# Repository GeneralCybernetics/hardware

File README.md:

### General Cybernetics Project PCBs & CAD Models

**TODO**
- [ ] move big files to git-lfs
- [ ] move current STM32 to STM32F407VGT6

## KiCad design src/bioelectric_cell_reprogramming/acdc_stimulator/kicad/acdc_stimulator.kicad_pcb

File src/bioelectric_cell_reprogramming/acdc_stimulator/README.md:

# Ion Concentration Biomodulator
The Ion Concentration Biomodulator can precisely alter the ionic composition of extracellular fluid to modulate the $$V_{mem}$$ of cells.

### Links
- [Parts list](https://docs.google.com/spreadsheets/d/1BXY7yvE0v-gVbK3v_EXQUiAxz3EebexK3CFEh7COzpo/edit?usp=sharing) (non-PCB)

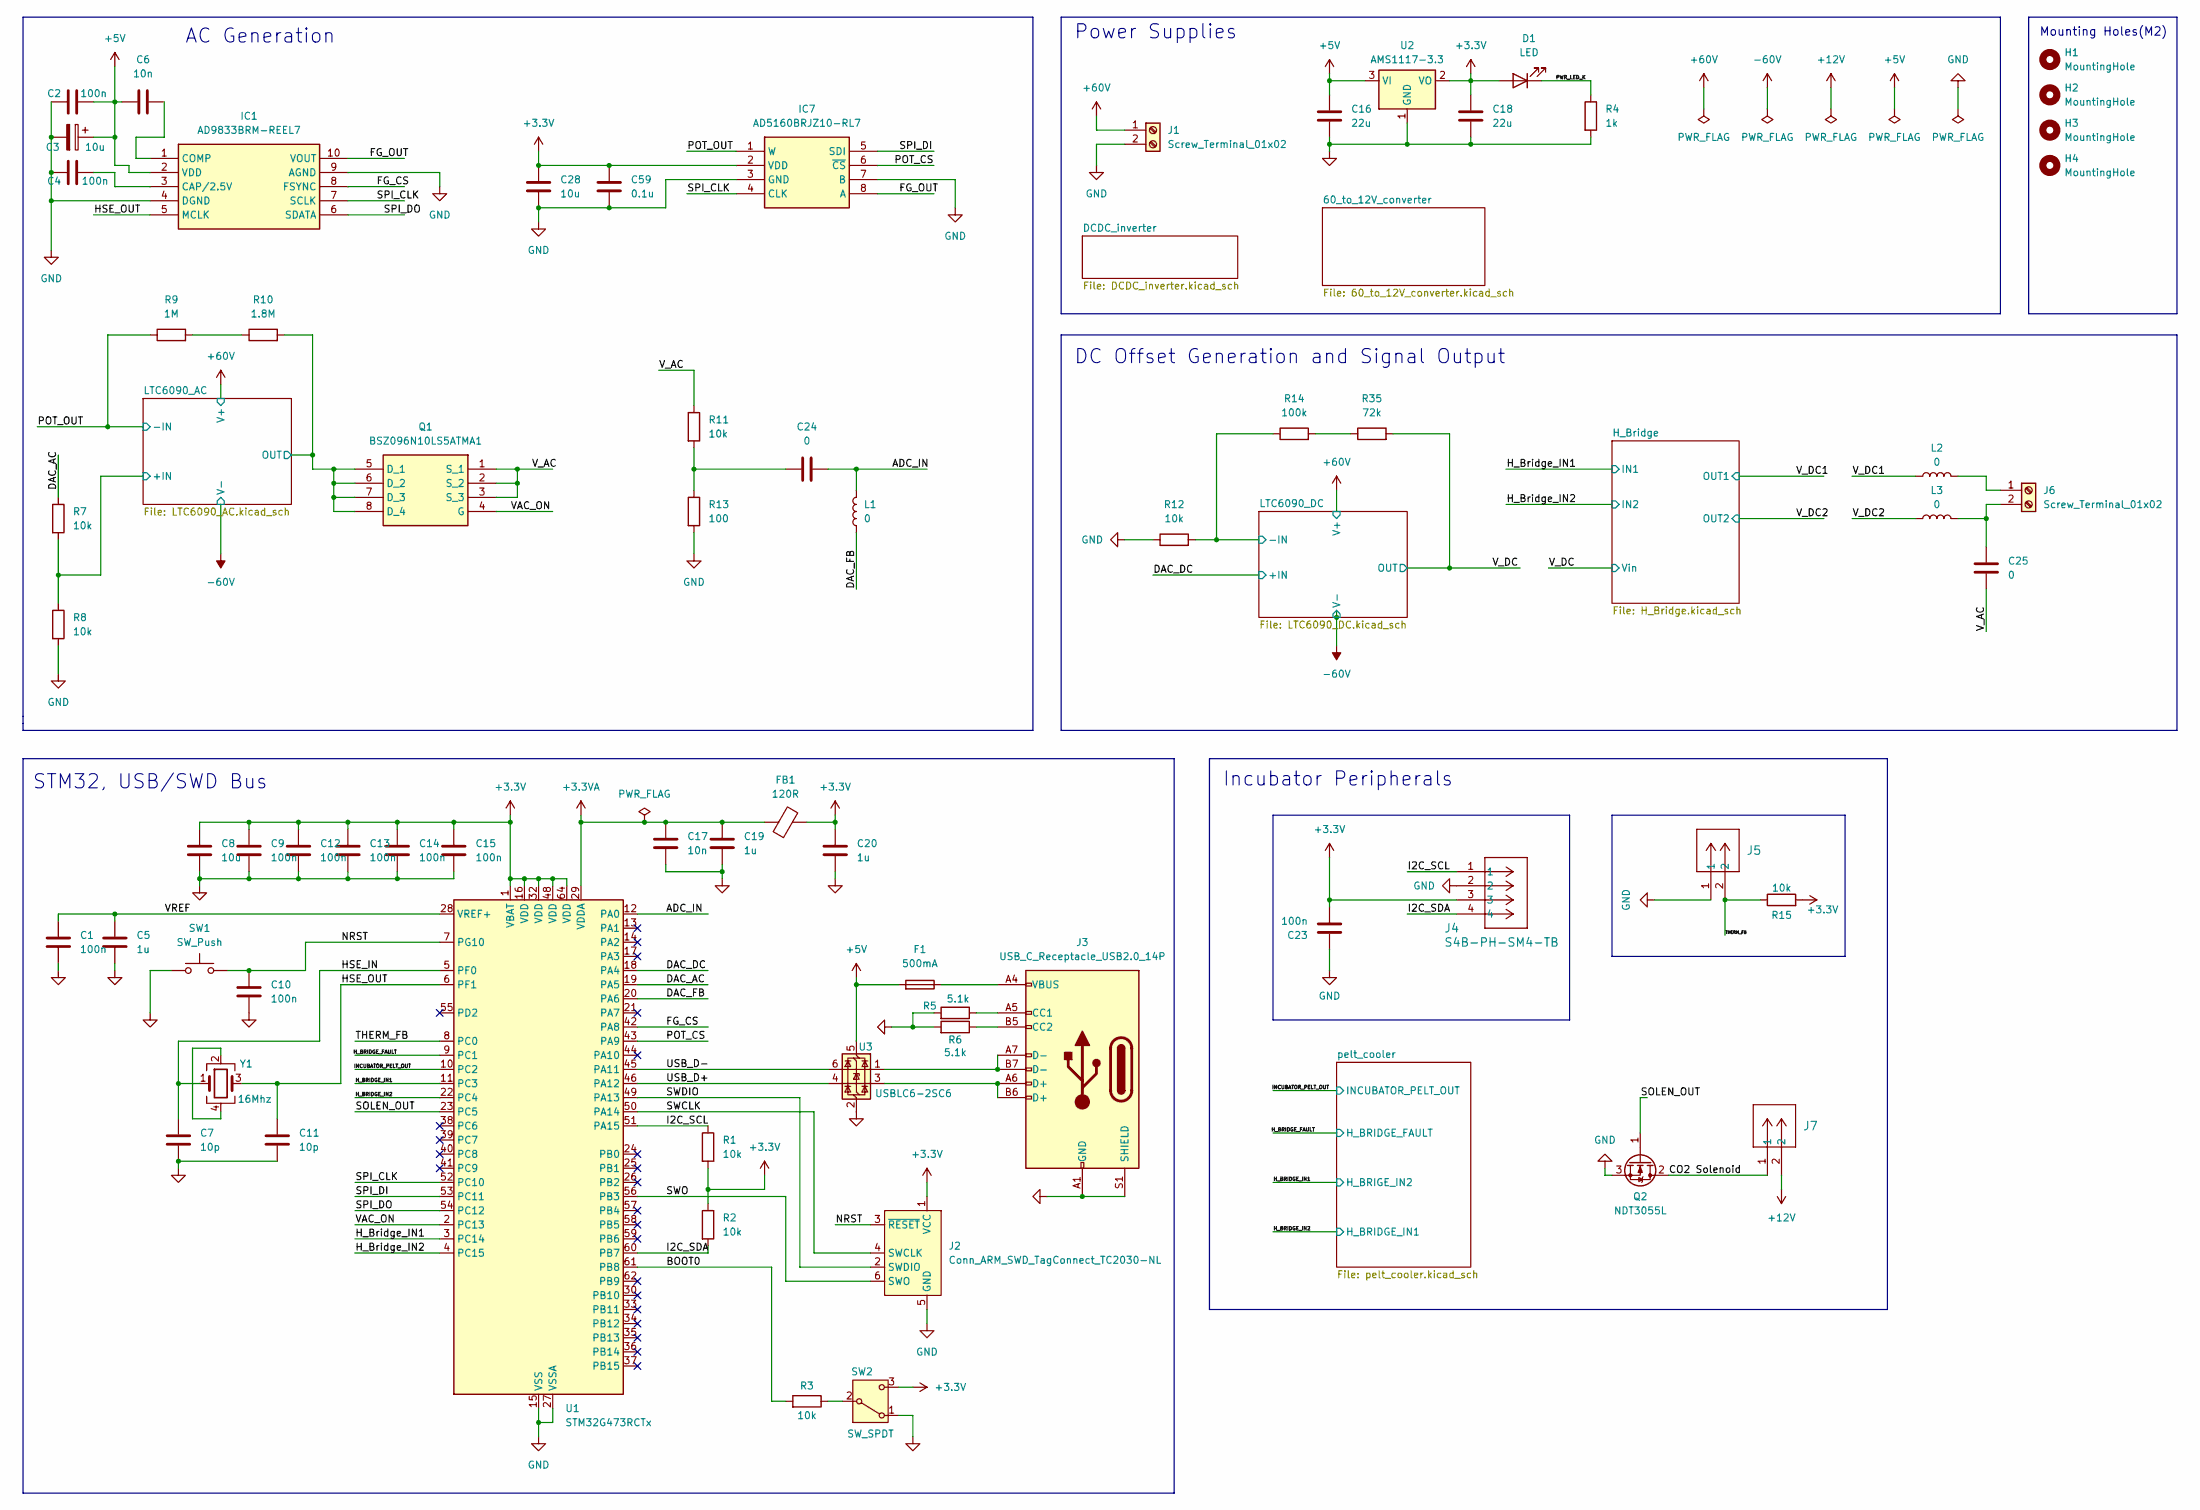
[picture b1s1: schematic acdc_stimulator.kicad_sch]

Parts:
C1, C2, C4, C9, C10, C12, C13, C14, C15, C23: 100n; C_0402_1005Metric; Manufacturer Part Number GRM155R62A104KE14D
C3: 10u; CP_Elec_5x5.4; Manufacturer Part Number FVH050ADA100M0554
C5, C19, C20: 1u; C_0402_1005Metric; Manufacturer Part Number CL05A105KO5NNNC
C6, C17: 10n; C_0201_0603Metric; Manufacturer Part Number GRM033R61E103KA12D
C7, C11: 10p; C_0201_0603Metric; Manufacturer Part Number GRM0335C1H300GA01D
C8, C28: 10u; C_0603_1608Metric; Manufacturer Part Number CL10A106MQ8NNNC
C16, C18: 22u; C_0805_2012Metric; Manufacturer Part Number CL21A226MQQNNNE
C24, C25: 0; C_Disc_D7.5mm_W2.5mm_P5.00mm
C59: 0.1u; C_0402_1005Metric; Manufacturer Part Number GRM155R62A104KE14D
D1: LED; LED_0402_1005Metric; Manufacturer Part Number 16-213SDRC/S530-A3/TR8
F1: 500mA; Fuse_0603_1608Metric; Manufacturer Part Number SMD0603P050TF
FB1: 120R; L_0603_1608Metric; Manufacturer Part Number BLM18PG121SN1D
H1, H2, H3, H4: MountingHole; MountingHole_2.7mm_M2.5
IC1: AD9833BRM-REEL7; SOP50P490X110-10N; Manufacturer_Part_Number AD9833BRM-REEL7; Mouser Part Number 584-AD9833BRM-R7
IC7: AD5160BRJZ10-RL7; SOT65P280X145-8N; Manufacturer_Part_Number AD5160BRJZ10-RL7; Mouser Part Number 584-AD5160BRJZ10-R7
J1, J6: Screw_Terminal_01x02; TerminalBlock_Altech_AK300-2_P5.00mm; Manufacturer Part Number 30.602/BLUE
J2: Conn_ARM_SWD_TagConnect_TC2030-NL; Tag-Connect_TC2030-IDC-NL_2x03_P1.27mm_Vertical
J3: USB_C_Receptacle_USB2.0_14P; USB_C_Receptacle_XKB_U262-16XN-4BVC11; Manufacturer Part Number U262-161N-4BVC11
J4: S4B-PH-SM4-TB; CONN4_S4B-PH-SM4-TB_JST; Manufacturer Part Number S4B-PH-SM4-TB(LF)(SN)
J5, J7: IPL1-102-01-L-S-K; CONN_IPL1-102-01-L-S-K_SAI; Manufacturer Part Number IPL1-102-01-L-S-K
L1, L2, L3: 0; L_Radial_D7.0mm_P3.00mm
Q1: BSZ096N10LS5ATMA1; BSZ060NE2LS; Manufacturer_Part_Number BSZ096N10LS5ATMA1; Mouser Part Number 726-BSZ096N10LS5ATMA
Q2: NDT3055L; SOT-223-3_TabPin2; Manufacturer Part Number NDT3055L
R1, R2, R3, R7, R8, R12, R15: 10k; R_0402_1005Metric; Manufacturer Part Number NQ02WGJ0103TCE
R4: 1k; R_0402_1005Metric; Manufacturer Part Number 0402WGF1001TCE
R5, R6: 5.1k; R_0201_0603Metric; Manufacturer Part Number RC0201JR-075K1L
R9: 1M; R_0805_2012Metric; Manufacturer Part Number 0805W8F1004T5E
R10: 1.8M; R_0805_2012Metric; Manufacturer Part Number 0805W8F1804T5E
R11: 10k; R_0805_2012Metric; Manufacturer Part Number QR0805J10K0P05Z
R13: 100; R_0805_2012Metric; Manufacturer Part Number 0805W8F1000T5E
R14: 100k; R_0603_1608Metric; Manufacturer Part Number RC0603FR-07100KL
R35: 72k; R_0603_1608Metric; Manufacturer Part Number AR03BTCX7202N
SW1: SW_Push; SW_Push_1P1T_NO_CK_KMR2; Manufacturer Part Number KMR231GLFS; JLCPCB Part # C99271
SW2: SW_SPDT; SW_SPDT_PCM12; Manufacturer Part Number PCM12SMTR
U1: STM32G473RCTx; LQFP-64_10x10mm_P0.5mm; Manufacturer Part Number STM32G473RCT6
U2: AMS1117-3.3; SOT-223-3_TabPin2; Manufacturer Part Number AMS1117-3.3
U3: USBLC6-2SC6; SOT-23-6; Manufacturer Part Number USBLC6-2SC6
Y1: 16Mhz; Crystal_SMD_3225-4Pin_3.2x2.5mm; Manufacturer Part Number 7M16000024

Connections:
+3.3V: C8.1, C9.1, C12.1, C13.1, C14.1, C15.1, C18.1, C20.1, C23.1, C28.1, C59.1, D1.2 (A), FB1.2, IC7.2 (VDD), J2.1 (VCC), J4.3, R1.2, R2.1, R15.2, SW2.3 (C), U1.1 (VBAT), U1.16 (VDD), U1.32 (VDD), U1.48 (VDD), U1.64 (VDD), U2.2 (VO)
+3.3VA: C17.1, C19.1, FB1.1, U1.29 (VDDA)
+5V: C2.2, C3.1, C6.1, C16.1, F1.2, IC1.2 (VDD), U2.3 (VI), U3.5 (VBUS); also elsewhere on the board
+12V: J7.2; also elsewhere on the board
+60V: J1.1; also elsewhere on the board
/ADC_IN: C24.2, L1.2, U1.12 (PA0)
/BOOT0: R3.2, U1.61 (PB8)
/CO2 Solenoid: J7.1, Q2.2 (D)
/DAC_AC: R7.1, U1.19 (PA5)
/DAC_DC: U1.18 (PA4); also elsewhere on the board
/DAC_FB: L1.1, U1.20 (PA6)
/FG_CS: IC1.8 (FSYNC), U1.42 (PA8)
/FG_OUT: IC1.10 (VOUT), IC7.8 (A)
/HSE_IN: C7.1, U1.5 (PF0), Y1.1
/HSE_OUT: C11.1, IC1.5 (MCLK), U1.6 (PF1), Y1.3
/H_BRIDGE_FAULT: U1.9 (PC1); also elsewhere on the board
/H_BRIDGE_IN1: U1.11 (PC3); also elsewhere on the board
/H_BRIDGE_IN2: U1.22 (PC4); also elsewhere on the board
/H_Bridge_IN1: U1.3 (PC14); also elsewhere on the board
/H_Bridge_IN2: U1.4 (PC15); also elsewhere on the board
/I2C_SCL: J4.1, R1.1, U1.51 (PA15)
/I2C_SDA: J4.4, R2.2, U1.60 (PB7)
/INCUBATOR_PELT_OUT: U1.10 (PC2); also elsewhere on the board
/LTC6090_AC/+IN: R7.2, R8.1; also elsewhere on the board
/LTC6090_AC/OUT: Q1.5 (D_1), Q1.6 (D_2), Q1.7 (D_3), Q1.8 (D_4), R10.2; also elsewhere on the board
/LTC6090_DC/-IN: R12.2, R14.1; also elsewhere on the board
/NRST: C10.1, J2.3 (~RESET), SW1.2, U1.7 (PG10)
/POT_CS: IC7.6 (~CS), U1.43 (PA9)
/POT_OUT: IC7.1 (W), R9.1; also elsewhere on the board
/PWR_LED_K: D1.1 (K), R4.1
/SOLEN_OUT: Q2.1 (G), U1.23 (PC5)
/SPI_CLK: IC1.7 (SCLK), IC7.4 (CLK), U1.52 (PC10)
/SPI_DI: IC7.5 (SDI), U1.53 (PC11)
/SPI_DO: IC1.6 (SDATA), U1.54 (PC12)
/SWCLK: J2.4 (SWCLK), U1.50 (PA14)
/SWDIO: J2.2 (SWDIO), U1.49 (PA13)
/SWO: J2.6 (SWO), U1.56 (PB3)
/THERM_FB: J5.2, R15.1, U1.8 (PC0)
/USB_D+: U1.46 (PA12), U3.4 (I/O2)
/USB_D-: U1.45 (PA11), U3.6 (I/O1)
/VAC_ON: Q1.4 (G), U1.2 (PC13)
/VREF: C1.1, C5.1, U1.28 (VREF+)
/V_AC: C25.2, Q1.1 (S_1), Q1.2 (S_2), Q1.3 (S_3), R11.1
/V_DC: R35.2; also elsewhere on the board
/V_DC1: L2.1; also elsewhere on the board
/V_DC2: L3.1; also elsewhere on the board
GND: C1.2, C2.1, C3.2, C4.1, C5.2, C7.2, C8.2, C9.2, C10.2, C11.2, C12.2, C13.2, C14.2, C15.2, C16.2, C17.2, C18.2, C19.2, C20.2, C23.2, C28.2, C59.2, IC1.4 (DGND), IC1.9 (AGND), IC7.3 (GND), IC7.7 (B), J1.2, J2.5 (GND), J3.A1 (GND), J3.A12 (GND), J3.B1 (GND), J3.B12 (GND), J3.S1 (SHIELD), J4.2, J5.1, Q2.3 (S), R4.2, R5.2, R6.2, R8.2, R12.1, R13.2, SW1.1, SW2.1 (A), U1.15 (VSS), U1.27 (VSSA), U1.31 (VSS), U1.47 (VSS), U1.63 (VSS), U2.1 (GND), U3.2 (GND); also elsewhere on the board
unnamed: C24.1, R11.2, R13.1
unnamed: F1.1, J3.A4 (VBUS), J3.A9 (VBUS), J3.B4 (VBUS), J3.B9 (VBUS)
unnamed: C4.2, IC1.3 (CAP/2.5V)
unnamed: C6.2, IC1.1 (COMP)
unnamed: J3.A5 (CC1), R5.1
unnamed: J3.B5 (CC2), R6.1
unnamed: J3.A6 (D+), J3.B6 (D+), U3.3 (I/O2)
unnamed: J3.A7 (D-), J3.B7 (D-), U3.1 (I/O1)
unnamed: J6.1, L2.2
unnamed: C25.1, J6.2, L3.2
unnamed: R9.2, R10.1
unnamed: R14.2, R35.1
unnamed: R3.1, SW2.2 (B)
unnamed: Y1.2, Y1.4

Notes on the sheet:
Mounting Holes(M2)
Incubator Peripherals
STM32, USB/SWD Bus
DC Offset Generation and Signal Output
AC Generation
Power Supplies

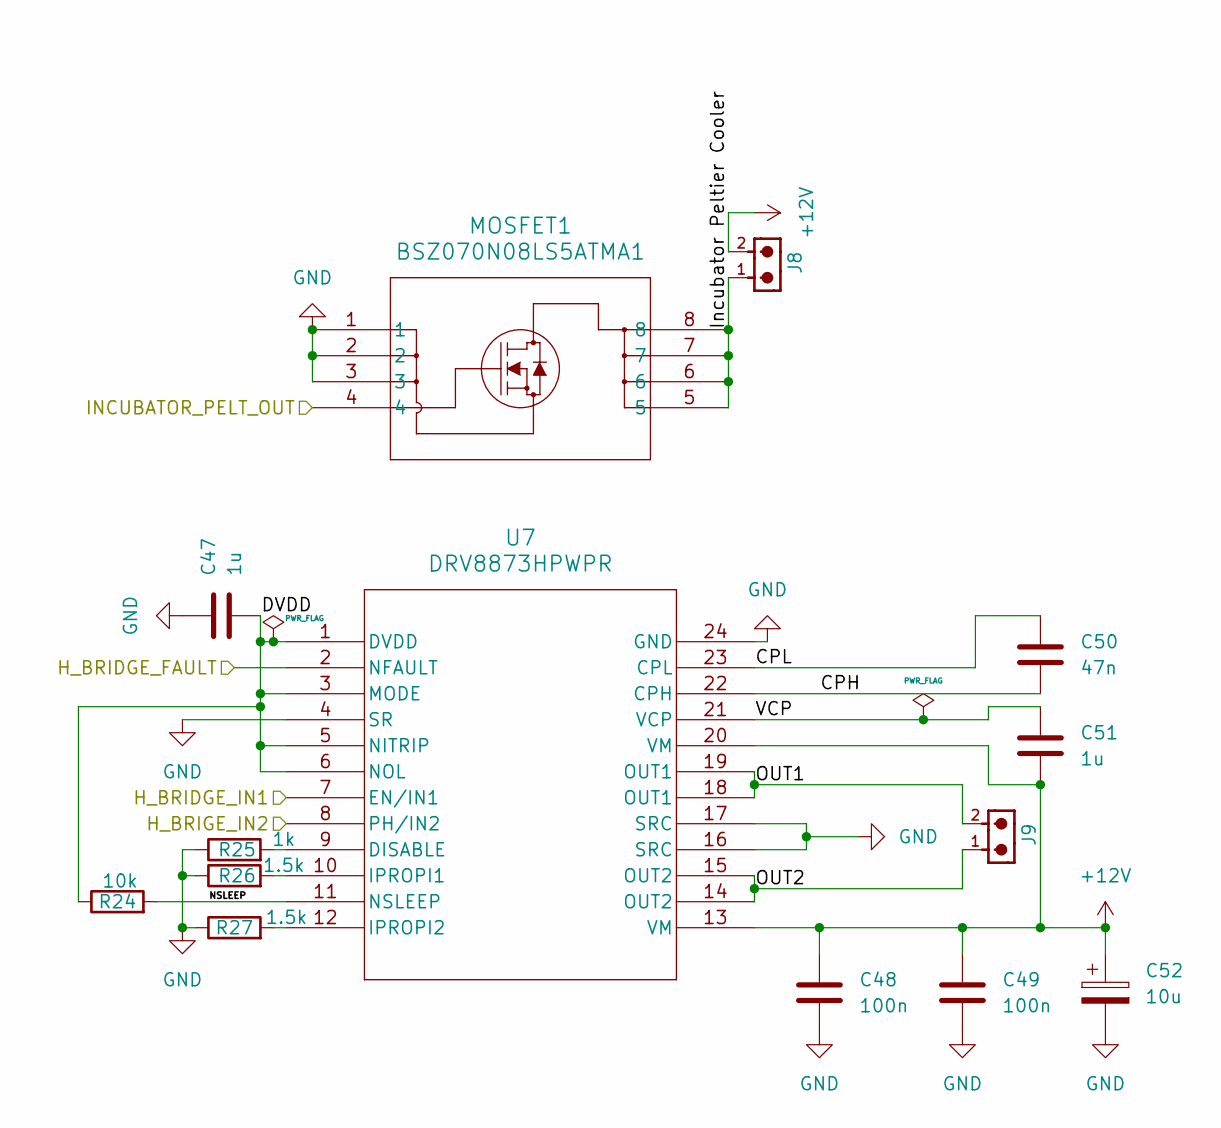
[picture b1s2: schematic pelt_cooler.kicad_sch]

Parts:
C47, C51: 1u; C_0402_1005Metric; Manufacturer Part Number CL05A105KO5NNNC
C48, C49: 100n; C_0402_1005Metric; Manufacturer Part Number GRM155R62A104KE14D
C50: 47n; C_0402_1005Metric; Manufacturer Part Number GRM155R71C473KA01D
C52: 10u; CP_Elec_5x5.4; Manufacturer Part Number FVH050ADA100M0554
J8, J9: 6620XX11122_66200211122; 66200211122; PART-NUMBER 66200211122
MOSFET1: BSZ070N08LS5ATMA1; TSDSON-8-FL_INF; Manufacturer Part Number BSZ070N08LS5
R24: 10k; R_0201_0603Metric; Manufacturer Part Number RTT01103JTH
R25: 1k; R_0201_0603Metric; Manufacturer Part Number CR0201FH1001G
R26, R27: 1.5k; R_0201_0603Metric; Manufacturer Part Number RC0201FR-071K5L
U7: DRV8873HPWPR; PWP24_TEX; Manufacturer Part Number DRV8873HPWPR

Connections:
+12V: C48.1, C49.1, C51.2, C52.1, J8.2, U7.13 (VM), U7.20 (VM); also elsewhere on the board
/H_BRIDGE_FAULT: U7.2 (NFAULT); also elsewhere on the board
/H_BRIDGE_IN1: U7.8 (PH/IN2); also elsewhere on the board
/H_BRIDGE_IN2: U7.7 (EN/IN1); also elsewhere on the board
/INCUBATOR_PELT_OUT: MOSFET1.4; also elsewhere on the board
/pelt_cooler/CPH: C50.2, U7.22 (CPH)
/pelt_cooler/CPL: C50.1, U7.23 (CPL)
/pelt_cooler/DVDD: C47.2, R24.1, U7.1 (DVDD), U7.3 (MODE), U7.5 (NITRIP), U7.6 (NOL)
/pelt_cooler/Incubator Peltier Cooler: J8.1, MOSFET1.5, MOSFET1.6, MOSFET1.7, MOSFET1.8
/pelt_cooler/NSLEEP: R24.2, U7.11 (NSLEEP)
/pelt_cooler/OUT1: J9.2, U7.18 (OUT1), U7.19 (OUT1)
/pelt_cooler/OUT2: J9.1, U7.14 (OUT2), U7.15 (OUT2)
/pelt_cooler/VCP: C51.1, U7.21 (VCP)
GND: C47.1, C48.2, C49.2, C52.2, MOSFET1.1, MOSFET1.2, MOSFET1.3, R25.1, R26.1, R27.1, U7.4 (SR), U7.16 (SRC), U7.17 (SRC), U7.24 (GND); also elsewhere on the board
unnamed: R25.2, U7.9 (DISABLE)
unnamed: R26.2, U7.10 (IPROPI1)
unnamed: R27.2, U7.12 (IPROPI2)

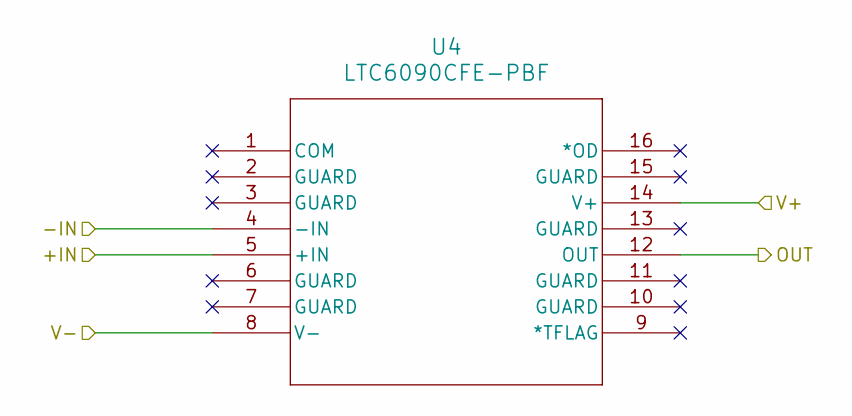
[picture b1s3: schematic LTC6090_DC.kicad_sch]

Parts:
U4: LTC6090CFE-PBF; TSSOP-16_FE&slash_BA_LIT; Manufacturer Part Number LTC6090CFE#PBF

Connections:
+60V: U4.14 (V+); also elsewhere on the board
-60V: U4.8 (V-); also elsewhere on the board
/DAC_DC: U4.5 (+IN); also elsewhere on the board
/LTC6090_DC/-IN: U4.4 (-IN); also elsewhere on the board
/V_DC: U4.12 (OUT); also elsewhere on the board

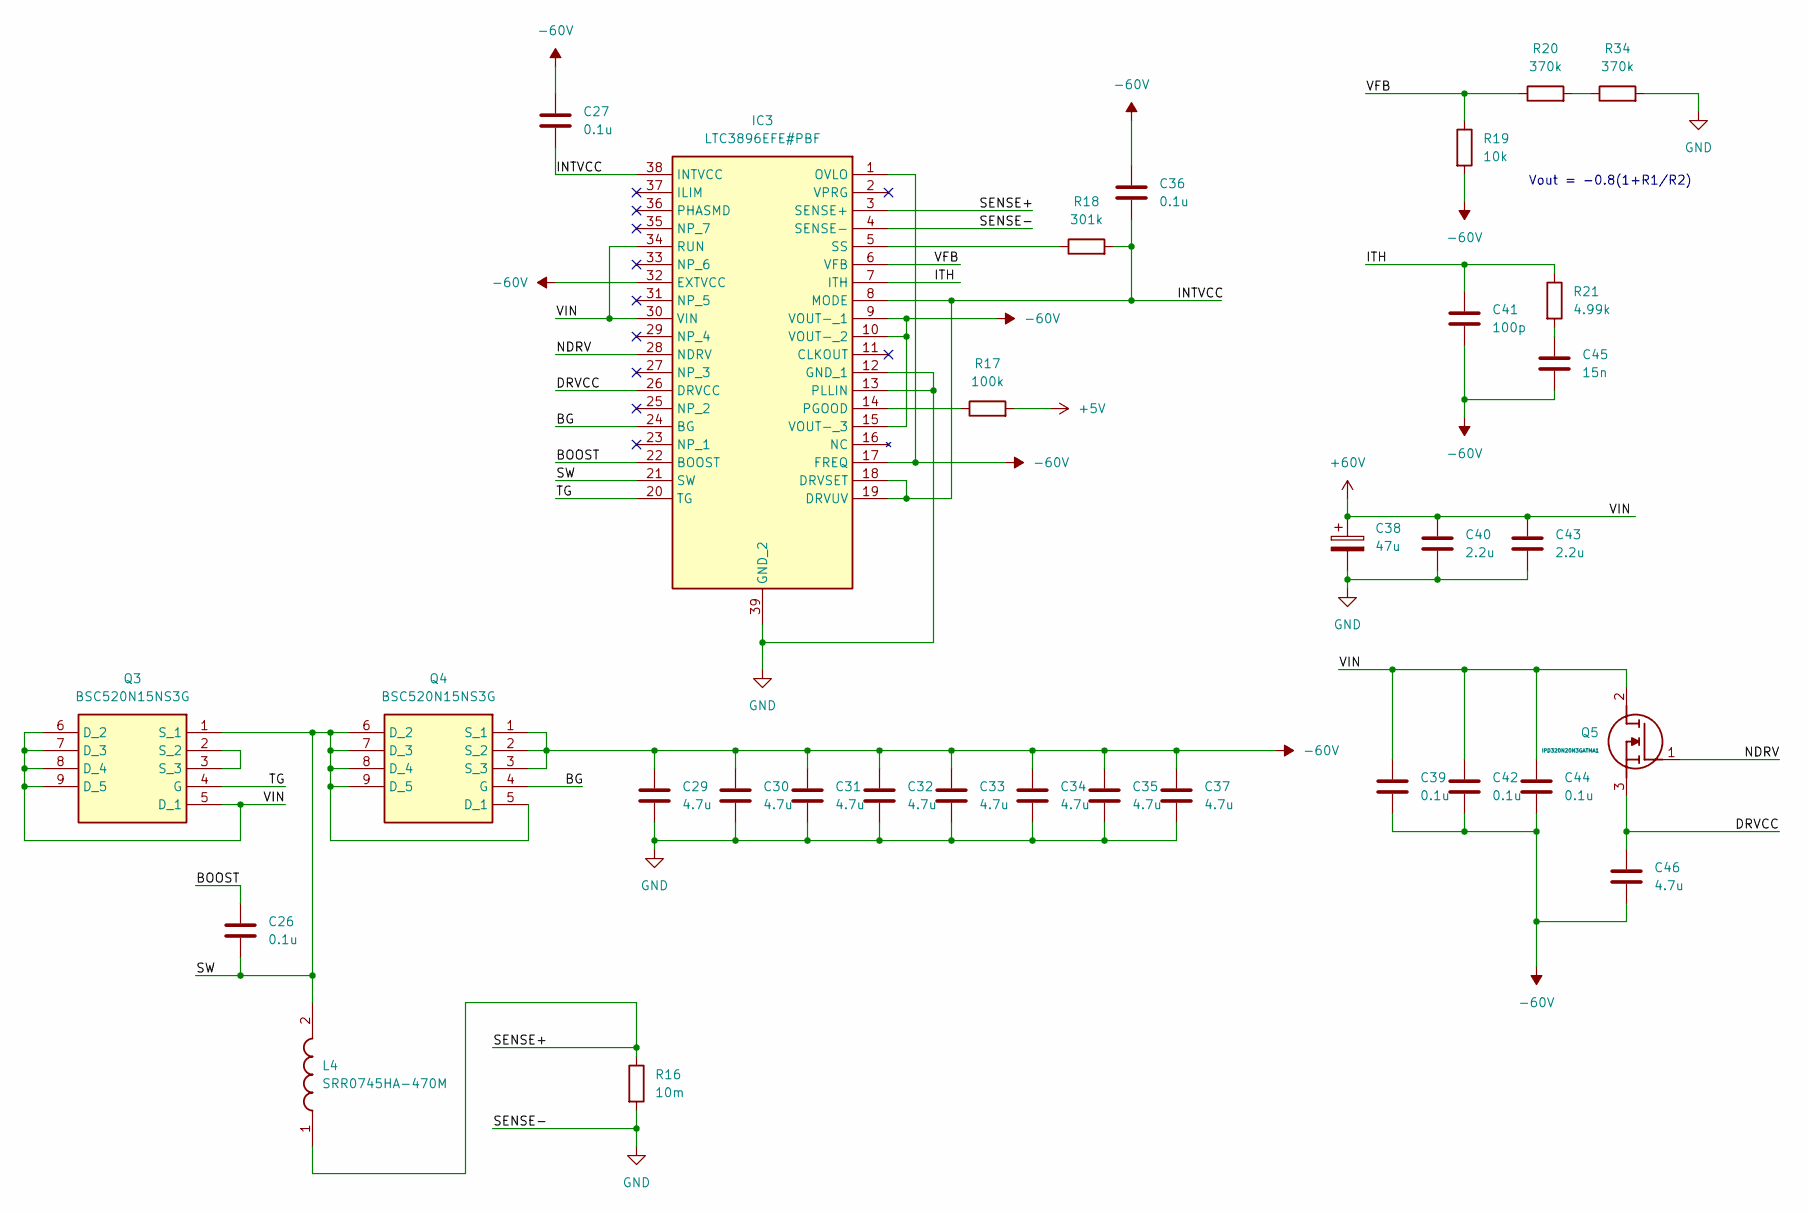
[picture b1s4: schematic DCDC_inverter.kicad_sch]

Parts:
C26, C27, C36, C39, C42, C44: 0.1u; C_0402_1005Metric; Manufacturer Part Number GRM155R62A104KE14D
C29, C30, C31, C32, C33, C34, C35, C37, C46: 4.7u; C_1206_3216Metric; Manufacturer Part Number GRM31CC72A475KE11L
C38: 47u; CP_Elec_10x10; Manufacturer Part Number VEJ470M2ATR-1010
C40, C43: 2.2u; C_0603_1608Metric; Manufacturer Part Number GRM21BD72A225KE01L
C41: 100p; C_0805_2012Metric; Manufacturer Part Number 0805CG101J101NT
C45: 15n; C_0805_2012Metric; Manufacturer Part Number 0805B153K101NT
IC3: LTC3896EFE#PBF; SOP50P640X120-39N; Manufacturer_Part_Number LTC3896EFE#PBF; Mouser Part Number 584-LTC3896EFE#PBF
L4: SRR0745HA-470M; SRR0745HA470M; Manufacturer_Part_Number SRR0745HA-470M; Mouser Part Number 652-SRR0745HA-470M
Q3, Q4: BSC520N15NS3G; BSC093N04LSG; Manufacturer_Part_Number BSC520N15NS3G
Q5: IPD320N20N3GATMA1; BTS3035TFATMA1; Manufacturer_Part_Number IPD320N20N3GATMA1; Mouser Part Number 726-IPD320N20N3GATMA
R16: 10m; R_1206_3216Metric; Manufacturer Part Number PMR18EZPFU10L0
R17: 100k; R_0603_1608Metric; Manufacturer Part Number RC0603FR-07100KL
R18: 301k; R_0603_1608Metric; Manufacturer Part Number RTT033013FTP
R19: 10k; R_0402_1005Metric; Manufacturer Part Number NQ02WGJ0103TCE
R20, R34: 370k; R_1206_3216Metric; Manufacturer Part Number SCR1206J370K
R21: 4.99k; R_0402_1005Metric; Manufacturer Part Number RK73H1ETTP4991F

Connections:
+5V: R17.2; also elsewhere on the board
+60V: C38.1, C39.1, C40.1, C42.1, C43.1, C44.1, IC3.30 (VIN), IC3.34 (RUN), Q3.5 (D_1), Q3.6 (D_2), Q3.7 (D_3), Q3.8 (D_4), Q3.9 (D_5), Q5.2 (D); also elsewhere on the board
-60V: C27.1, C29.1, C30.1, C31.1, C32.1, C33.1, C34.1, C35.1, C36.1, C37.1, C39.2, C41.2, C42.2, C44.2, C45.2, C46.2, IC3.1 (OVLO), IC3.9 (VOUT-_1), IC3.10 (VOUT-_2), IC3.15 (VOUT-_3), IC3.17 (FREQ), IC3.32 (EXTVCC), Q4.1 (S_1), Q4.2 (S_2), Q4.3 (S_3), R19.2; also elsewhere on the board
/DCDC_inverter/BG: IC3.24 (BG), Q4.4 (G)
/DCDC_inverter/BOOST: C26.1, IC3.22 (BOOST)
/DCDC_inverter/DRVCC: C46.1, IC3.26 (DRVCC), Q5.3 (S)
/DCDC_inverter/INTVCC: C27.2, C36.2, IC3.8 (MODE), IC3.18 (DRVSET), IC3.19 (DRVUV), IC3.38 (INTVCC), R18.2
/DCDC_inverter/ITH: C41.1, IC3.7 (ITH), R21.1
/DCDC_inverter/NDRV: IC3.28 (NDRV), Q5.1 (G)
/DCDC_inverter/SENSE+: IC3.3 (SENSE+), L4.1, R16.1
/DCDC_inverter/SW: C26.2, IC3.21 (SW), L4.2, Q3.1 (S_1), Q4.5 (D_1), Q4.6 (D_2), Q4.7 (D_3), Q4.8 (D_4), Q4.9 (D_5)
/DCDC_inverter/TG: IC3.20 (TG), Q3.4 (G)
/DCDC_inverter/VFB: IC3.6 (VFB), R19.1, R20.1
GND: C29.2, C30.2, C31.2, C32.2, C33.2, C34.2, C35.2, C37.2, C38.2, C40.2, C43.2, IC3.4 (SENSE-), IC3.12 (GND_1), IC3.13 (PLLIN), IC3.39 (GND_2), R16.2, R34.2; also elsewhere on the board
unnamed: C45.1, R21.2
unnamed: IC3.14 (PGOOD), R17.1
unnamed: IC3.5 (SS), R18.1
unnamed: Q3.2 (S_2), Q3.3 (S_3)
unnamed: R20.2, R34.1

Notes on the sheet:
Vout = -0.8(1+R1/R2)

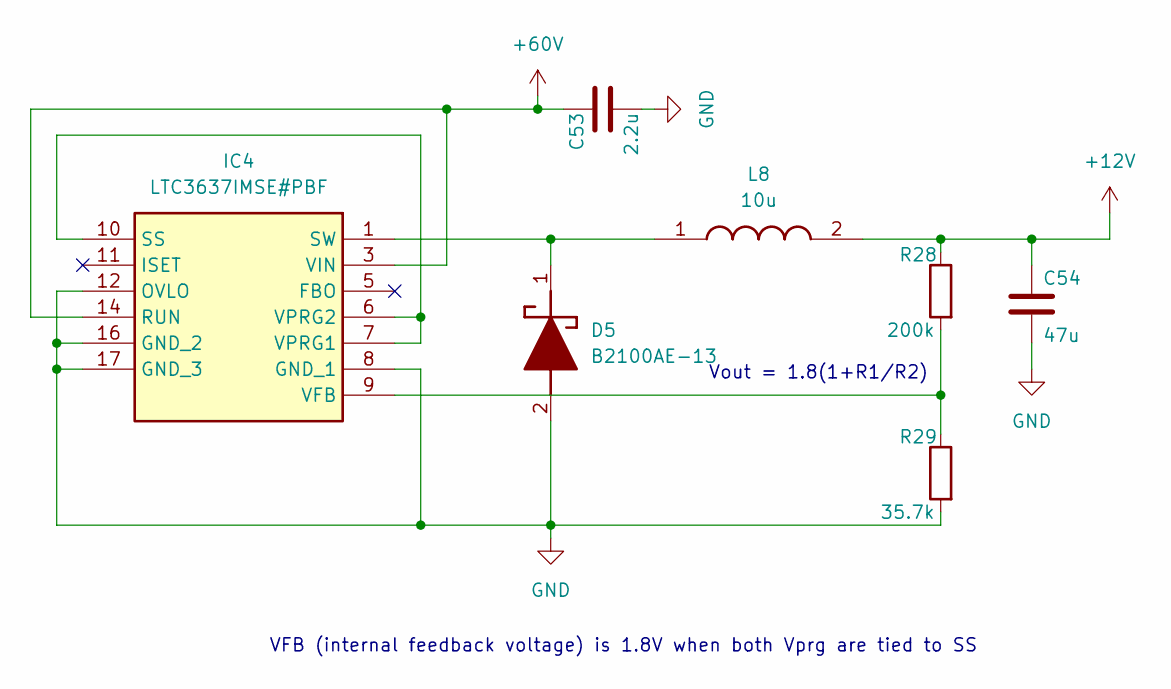
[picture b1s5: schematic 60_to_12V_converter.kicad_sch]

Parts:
C53: 2.2u; C_0603_1608Metric; Manufacturer Part Number GRM21BD72A225KE01L
C54: 47u; C_1206_3216Metric; Manufacturer Part Number 1206X476M160NT
D5: B2100AE-13; DIOM5226X240N; Manufacturer_Part_Number B2100AE-13; Mouser Part Number 621-B2100AE-13
IC4: LTC3637IMSE#PBF; LTC3637IMSEPBF; Manufacturer_Part_Number LTC3637IMSE#PBF; Mouser Part Number 584-LTC3637IMSE#PBF
L8: 10u; INDPM8080X420N; Manufacturer_Part_Number SWPA8040S100MT
R28: 200k; R_0603_1608Metric; Manufacturer Part Number 0603WAF2003T5E
R29: 35.7k; R_0603_1608Metric; Manufacturer Part Number 0603WAF3572T5E

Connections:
+12V: C54.1, L8.2, R28.1; also elsewhere on the board
+60V: C53.1, IC4.3 (VIN), IC4.14 (RUN); also elsewhere on the board
GND: C53.2, C54.2, D5.2 (A), IC4.8 (GND_1), IC4.12 (OVLO), IC4.16 (GND_2), IC4.17 (GND_3), R29.2; also elsewhere on the board
unnamed: D5.1 (K), IC4.1 (SW), L8.1
unnamed: IC4.6 (VPRG2), IC4.7 (VPRG1), IC4.10 (SS)
unnamed: IC4.9 (VFB), R28.2, R29.1

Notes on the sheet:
VFB (internal feedback voltage) is 1.8V when both Vprg are tied to SS
Vout = 1.8(1+R1/R2)

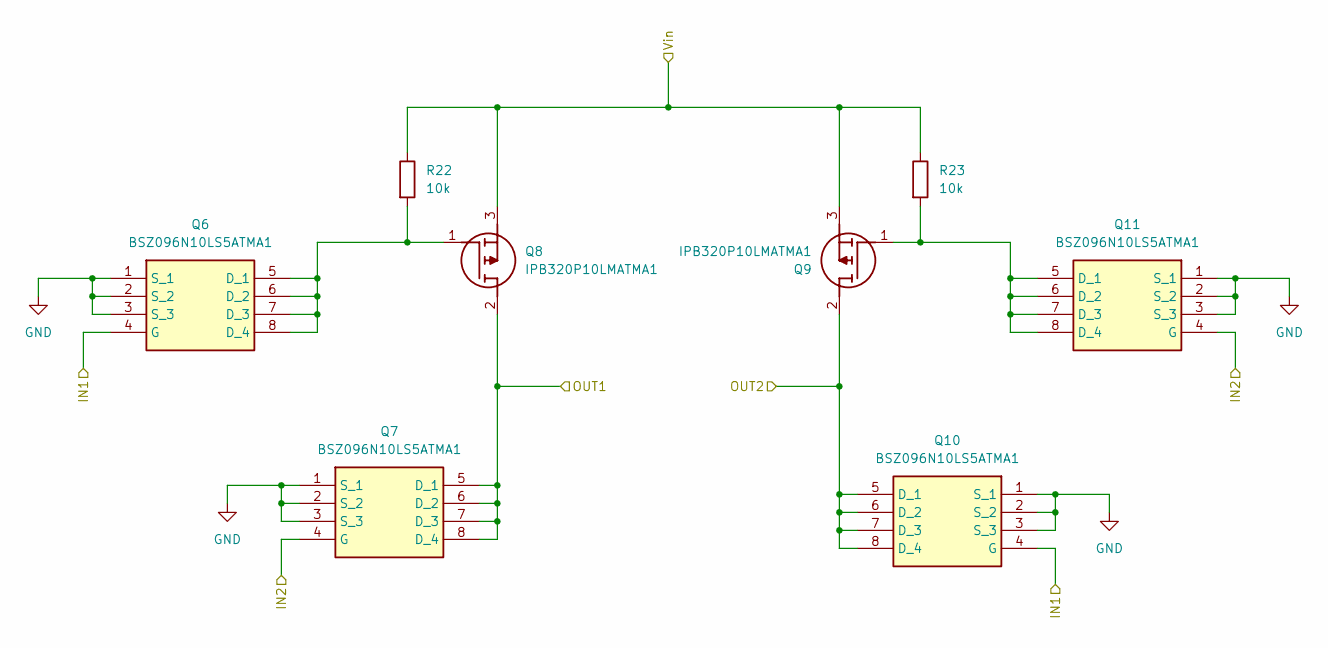
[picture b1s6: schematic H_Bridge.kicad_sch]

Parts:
Q6, Q7, Q10, Q11: BSZ096N10LS5ATMA1; BSZ060NE2LS; Manufacturer_Part_Number BSZ096N10LS5ATMA1; Mouser Part Number 726-BSZ096N10LS5ATMA
Q8, Q9: IPB320P10LMATMA1; Manufacturer_Part_Number IPB320P10LMATMA1
R22, R23: 10k; R_0402_1005Metric; Manufacturer Part Number NQ02WGJ0103TCE

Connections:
/H_Bridge_IN1: Q6.4 (G), Q10.4 (G); also elsewhere on the board
/H_Bridge_IN2: Q7.4 (G), Q11.4 (G); also elsewhere on the board
/V_DC: Q8.3 (S), Q9.3 (S), R22.1, R23.1; also elsewhere on the board
/V_DC1: Q7.5 (D_1), Q7.6 (D_2), Q7.7 (D_3), Q7.8 (D_4), Q8.2 (D); also elsewhere on the board
/V_DC2: Q9.2 (D), Q10.5 (D_1), Q10.6 (D_2), Q10.7 (D_3), Q10.8 (D_4); also elsewhere on the board
GND: Q6.1 (S_1), Q6.2 (S_2), Q6.3 (S_3), Q7.1 (S_1), Q7.2 (S_2), Q7.3 (S_3), Q10.1 (S_1), Q10.2 (S_2), Q10.3 (S_3), Q11.1 (S_1), Q11.2 (S_2), Q11.3 (S_3); also elsewhere on the board
unnamed: Q6.5 (D_1), Q6.6 (D_2), Q6.7 (D_3), Q6.8 (D_4), Q8.1 (G), R22.2
unnamed: Q9.1 (G), Q11.5 (D_1), Q11.6 (D_2), Q11.7 (D_3), Q11.8 (D_4), R23.2

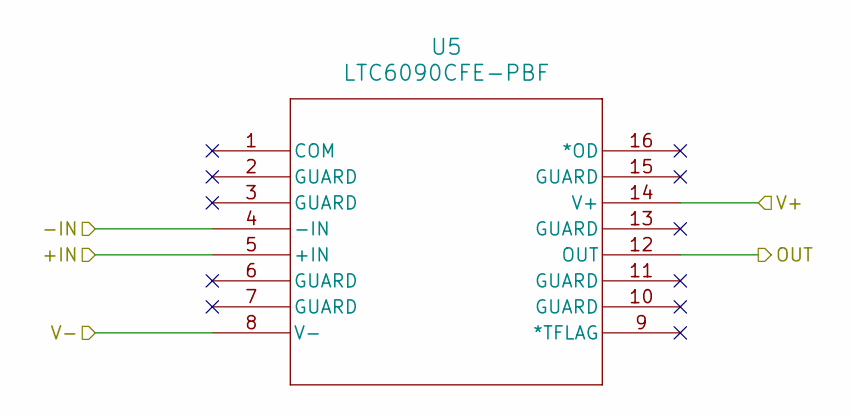
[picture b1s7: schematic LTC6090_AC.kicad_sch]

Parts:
U5: LTC6090CFE-PBF; TSSOP-16_FE&slash_BA_LIT; Manufacturer Part Number LTC6090CFE#PBF

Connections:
+60V: U5.14 (V+); also elsewhere on the board
-60V: U5.8 (V-); also elsewhere on the board
/LTC6090_AC/+IN: U5.5 (+IN); also elsewhere on the board
/LTC6090_AC/OUT: U5.12 (OUT); also elsewhere on the board
/POT_OUT: U5.4 (-IN); also elsewhere on the board

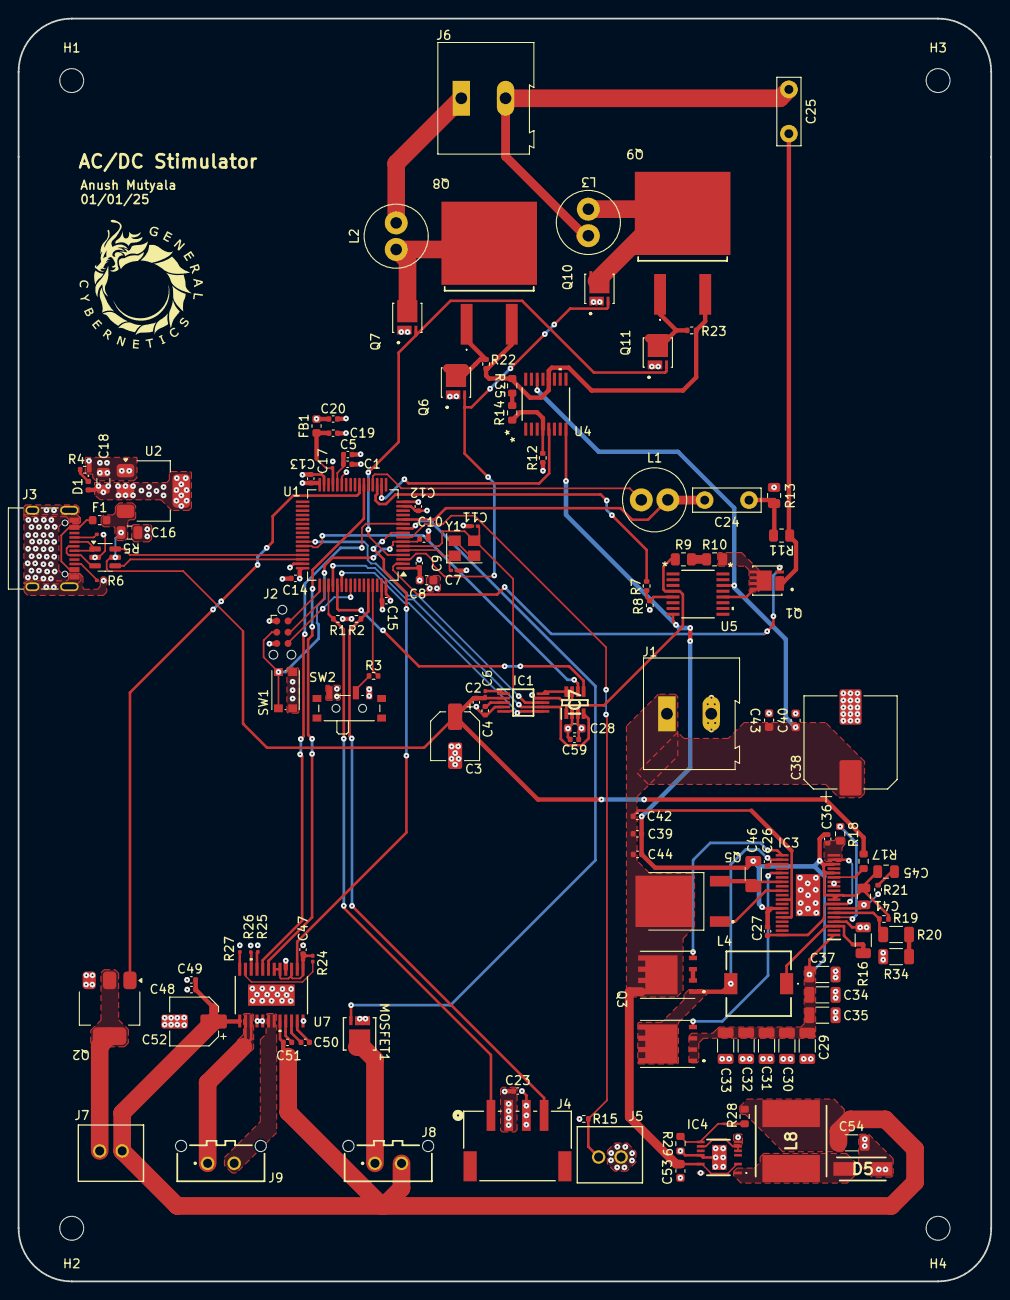
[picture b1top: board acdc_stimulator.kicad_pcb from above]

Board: 4 copper layers, 109.8 x 142.6 mm, 131 parts (0 on the bottom side), 93 nets.
